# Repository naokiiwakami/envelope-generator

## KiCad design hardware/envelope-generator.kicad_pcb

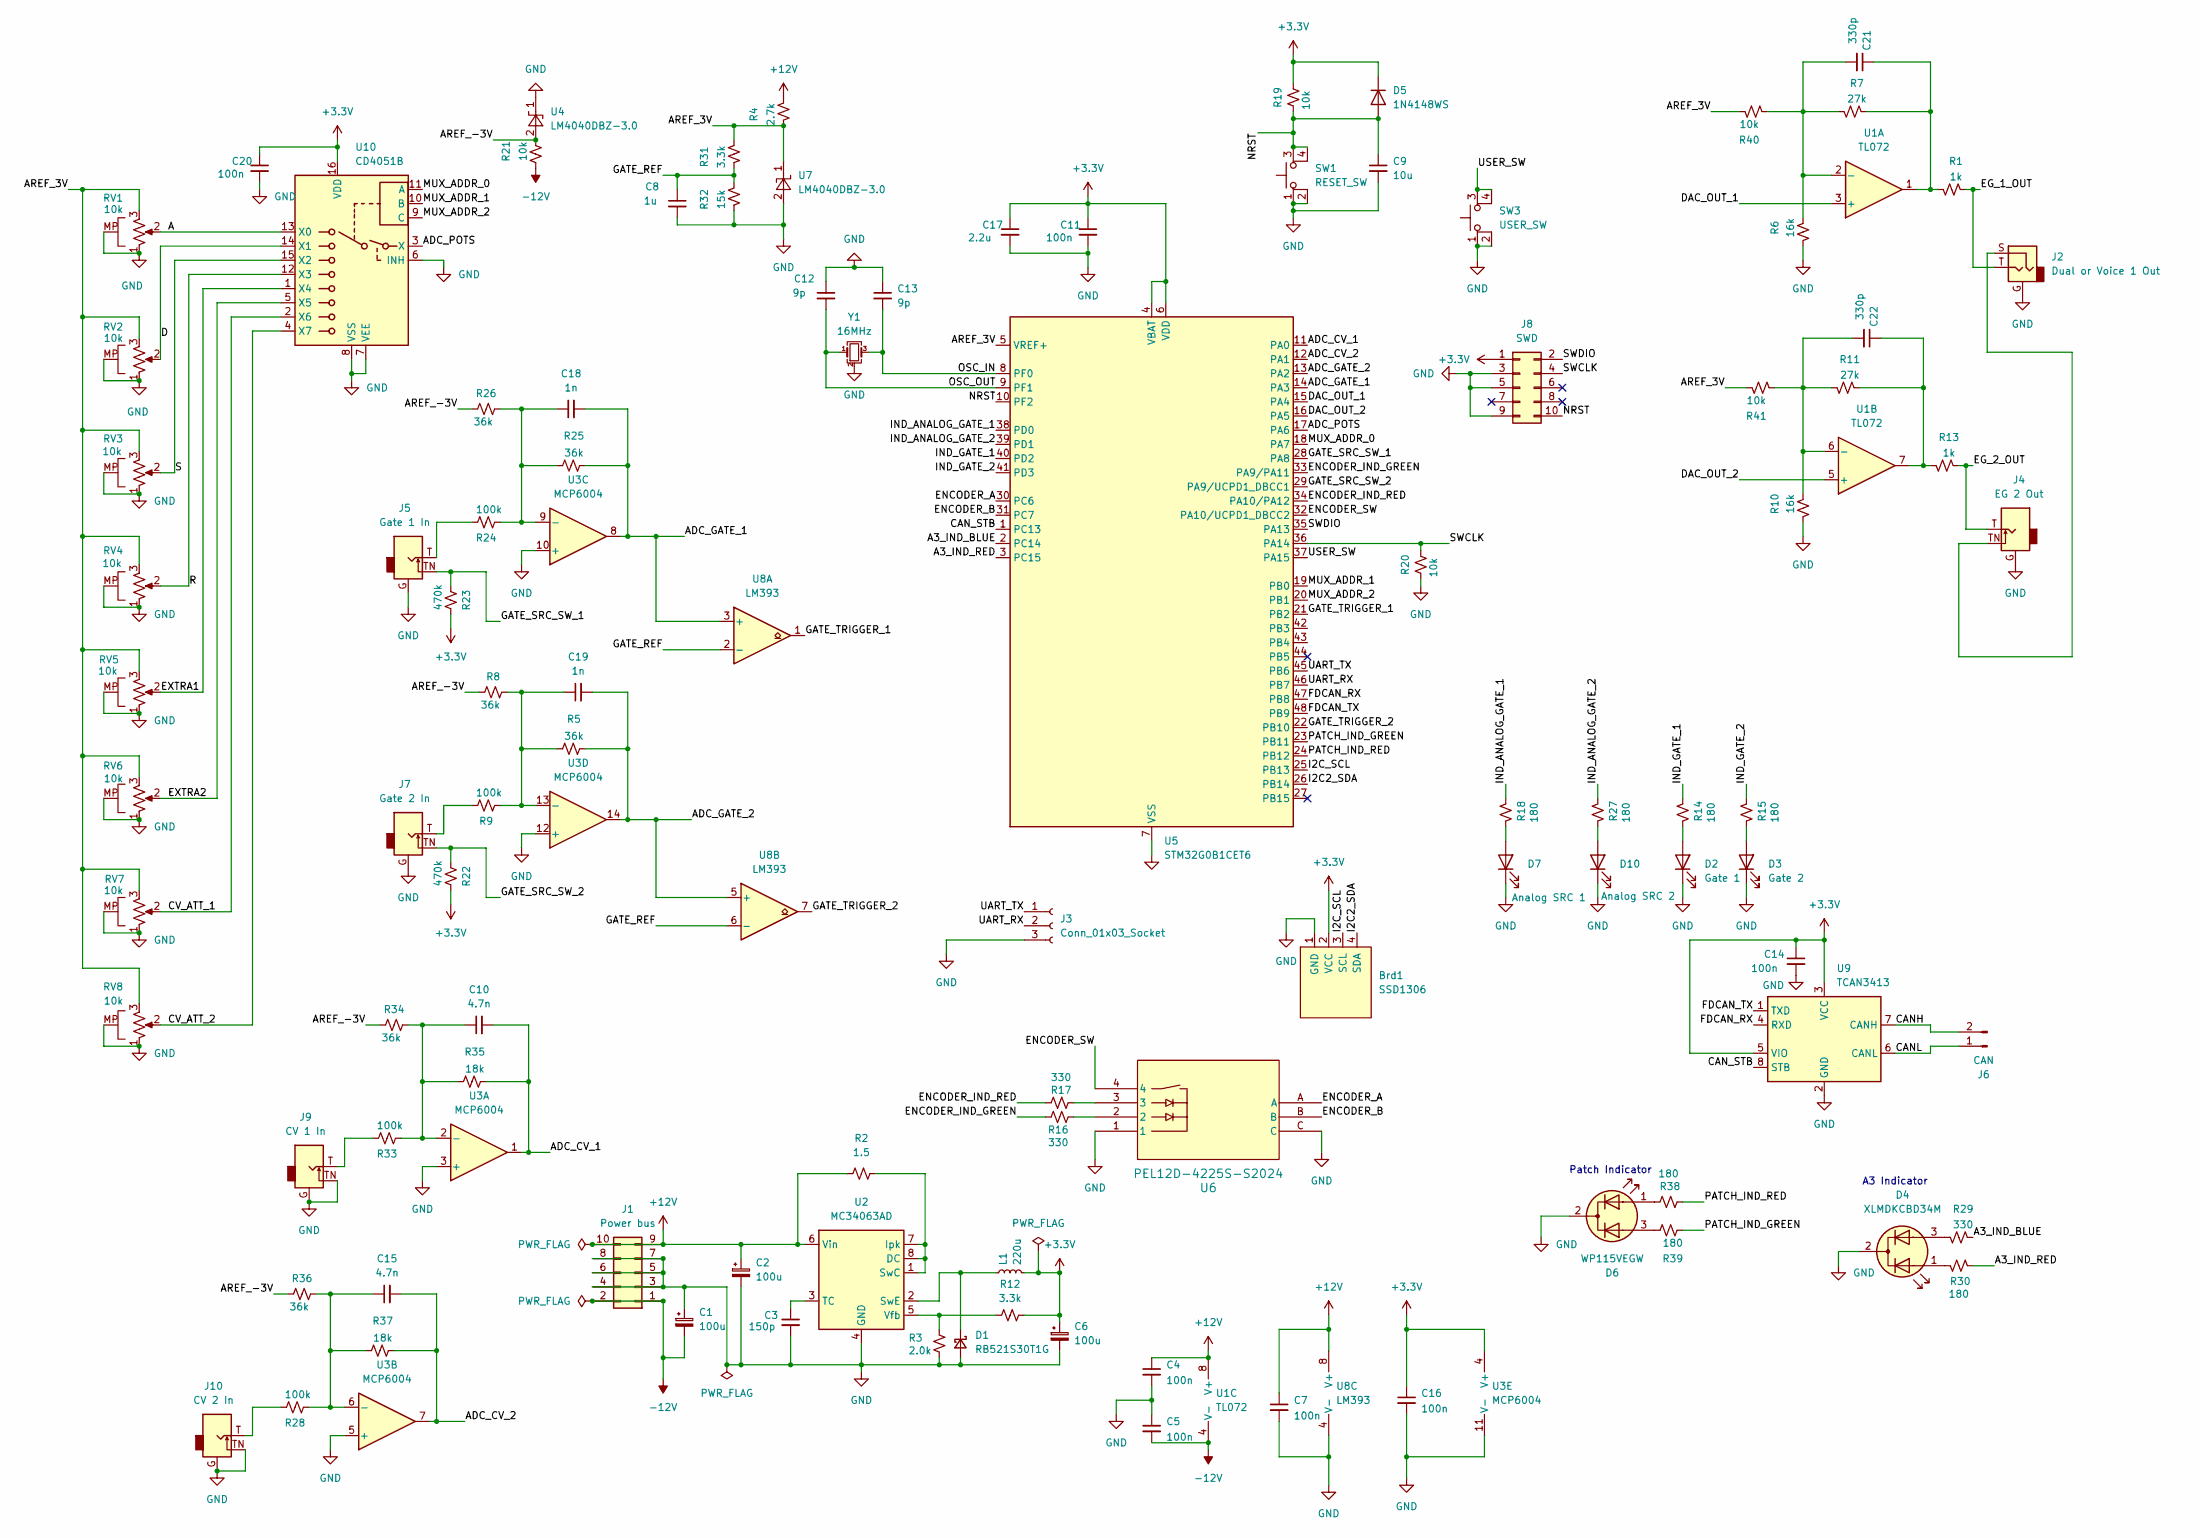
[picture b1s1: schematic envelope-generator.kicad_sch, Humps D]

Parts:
Brd1: SSD1306; 128x64OLED_aki
C1, C2, C6: 100u; CP_Elec_6.3x5.4_Nichicon
C3: 150p; C_0603_1608Metric
C4, C5, C7, C16: 100n; C_0603_1608Metric
C8: 1u; C_0603_1608Metric_Pad1.08x0.95mm_HandSolder
C9: 10u; C_0805_2012Metric
C10, C15: 4.7n; C_0603_1608Metric_Pad1.08x0.95mm_HandSolder
C11, C14, C20: 100n; C_0603_1608Metric_Pad1.08x0.95mm_HandSolder
C12, C13: 9p; C_0603_1608Metric_Pad1.08x0.95mm_HandSolder
C17: 2.2u; C_0603_1608Metric_Pad1.08x0.95mm_HandSolder
C18, C19: 1n; C_0603_1608Metric_Pad1.08x0.95mm_HandSolder
C21, C22: 330p; C_0603_1608Metric_Pad1.08x0.95mm_HandSolder
D1: RB521S30T1G; D_SOD-523
D2: Gate 1; LED_D3.0mm
D3: Gate 2; LED_D3.0mm
D4: XLMDKCBD34M; LED-3.0mm-3
D5: 1N4148WS; D_SOD-323
D6: WP115VEGW; LED-3.0mm-3
D7: Analog SRC 1; LED_D3.0mm
D10: Analog SRC 2; LED_D3.0mm
J1: Power bus; IDC-Header_2x05_P2.54mm_Vertical
J2: Dual or Voice 1 Out; Thonkiconn_Stereo
J3: Conn_01x03_Socket; PinSocket_1x03_P1.27mm_Vertical
J4: EG 2 Out; Thonkiconn
J5: Gate 1 In; Thonkiconn
J6: CAN; Molex_KK-254_AE-6410-02A_1x02_P2.54mm_Vertical
J7: Gate 2 In; Thonkiconn
J8: SWD; CONN_2x10_3220-10-0100-00_CNC
J9: CV 1 In; Thonkiconn
J10: CV 2 In; Thonkiconn
L1: 220u; L_1210_3225Metric
R1, R13: 1k; R_0603_1608Metric
R2: 1.5; R_0603_1608Metric
R3: 2.0k; R_0603_1608Metric
R4: 2.7k; R_0603_1608Metric_Pad0.98x0.95mm_HandSolder
R5, R8, R25, R26, R34, R36: 36k; R_0603_1608Metric_Pad0.98x0.95mm_HandSolder
R6, R10: 16k; R_0603_1608Metric
R7, R11: 27k; R_0603_1608Metric
R9, R24, R28, R33: 100k; R_0603_1608Metric_Pad0.98x0.95mm_HandSolder
R12: 3.3k; R_0603_1608Metric
R14, R15, R18, R27, R30: 180; R_0603_1608Metric
R16, R17, R29: 330; R_0603_1608Metric
R19, R20, R21: 10k; R_0603_1608Metric_Pad0.98x0.95mm_HandSolder
R22, R23: 470k; R_0603_1608Metric_Pad0.98x0.95mm_HandSolder
R31: 3.3k; R_0603_1608Metric_Pad0.98x0.95mm_HandSolder
R32: 15k; R_0603_1608Metric_Pad0.98x0.95mm_HandSolder
R35, R37: 18k; R_0603_1608Metric_Pad0.98x0.95mm_HandSolder
R38, R39: 180; R_0603_1608Metric_Pad0.98x0.95mm_HandSolder
R40, R41: 10k; R_0603_1608Metric
RV1, RV2, RV3, RV4, RV5, RV6, RV7, RV8: 10k; ALPHA_9MM
SW1: RESET_SW; Panasonic_EVQ_Q2
SW3: USER_SW; SW4_1825910-B_TEC
U1: TL072; SOT-23-8
U2: MC34063AD; SOIC-8_3.9x4.9mm_P1.27mm
U3: MCP6004; SOIC-14_3.9x8.7mm_P1.27mm
U4, U7: LM4040DBZ-3.0; SOT-23
U5: STM32G0B1CET6; LQFP-48_7x7mm_P0.5mm
U6: PEL12D-4225S-S2024; TO_4225S-S2024
U8: LM393; SOIC-8_3.9x4.9mm_P1.27mm
U9: TCAN3413; TSOT-23-8
U10: CD4051B; TSSOP-16_4.4x5mm_P0.65mm
Y1: 16MHz; Crystal_SMD_Abracon_ABM8G-4Pin_3.2x2.5mm

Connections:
+3.3V: Brd1.2 (VCC), C6.1, C11.1, C14.1, C16.1, C17.1, C20.1, D5.1 (K), J8.1, L1.2, R12.1, R19.2, R22.2, R23.2, U3.4 (V+), U5.4 (VBAT), U5.6 (VDD), U9.3 (VCC), U9.5 (VIO), U10.16 (VDD)
+12V: C2.1, C4.1, C7.1, J1.9, J1.10, R2.1, R4.2, U1.8 (V+), U2.6 (Vin), U8.8 (V+)
-12V: C1.2, C5.2, J1.1, J1.2, R21.2, U1.4 (V-)
/A: RV1.2, U10.13 (X0)
/A3_IND_BLUE: R29.1, U5.2 (PC14)
/A3_IND_RED: R30.1, U5.3 (PC15)
/ADC_CV_1: C10.2, R35.1, U3.1, U5.11 (PA0)
/ADC_CV_2: C15.2, R37.1, U3.7, U5.12 (PA1)
/ADC_GATE_1: C18.2, R25.1, U3.8, U5.14 (PA3), U8.3 (+)
/ADC_GATE_2: C19.2, R5.1, U3.14, U5.13 (PA2), U8.5 (+)
/ADC_POTS: U5.17 (PA6), U10.3 (X)
/AREF_3V: R4.1, R31.2, R40.1, R41.1, RV1.3, RV2.3, RV3.3, RV4.3, RV5.3, RV6.3, RV7.3, RV8.3, U5.5 (VREF+), U7.1 (K)
/AREF_-3V: R8.1, R21.1, R26.1, R34.1, R36.1, U4.2 (A)
/CANH: J6.2, U9.7 (CANH)
/CANL: J6.1, U9.6 (CANL)
/CAN_STB: U5.1 (PC13), U9.8 (STB)
/CV_ATT_1: RV7.2, U10.2 (X6)
/CV_ATT_2: RV8.2, U10.4 (X7)
/D: RV2.2, U10.14 (X1)
/DAC_OUT_1: U1.3 (+), U5.15 (PA4)
/DAC_OUT_2: U1.5 (+), U5.16 (PA5)
/EG_1_OUT: J2.T, R1.1
/EG_2_OUT: J4.T, R13.1
/ENCODER_A: U5.30 (PC6), U6.A
/ENCODER_B: U5.31 (PC7), U6.B
/ENCODER_IND_GREEN: R16.1, U5.33 (PA9/PA11)
/ENCODER_IND_RED: R17.2, U5.34 (PA10/PA12)
/ENCODER_SW: U5.32 (PA10/UCPD1_DBCC2), U6.4
/EXTRA1: RV5.2, U10.1 (X4)
/EXTRA2: RV6.2, U10.5 (X5)
/FDCAN_RX: U5.47 (PB8), U9.4 (RXD)
/FDCAN_TX: U5.48 (PB9), U9.1 (TXD)
/GATE_REF: C8.1, R31.1, R32.2, U8.2 (-), U8.6 (-)
/GATE_SRC_SW_1: J5.TN, R23.1, U5.28 (PA8)
/GATE_SRC_SW_2: J7.TN, R22.1, U5.29 (PA9/UCPD1_DBCC1)
/GATE_TRIGGER_1: U5.21 (PB2), U8.1
/GATE_TRIGGER_2: U5.22 (PB10), U8.7
/I2C2_SDA: Brd1.4 (SDA), U5.26 (PB14)
/I2C_SCL: Brd1.3 (SCL), U5.25 (PB13)
/IND_ANALOG_GATE_1: R18.1, U5.38 (PD0)
/IND_ANALOG_GATE_2: R27.1, U5.39 (PD1)
/IND_GATE_1: R14.1, U5.40 (PD2)
/IND_GATE_2: R15.1, U5.41 (PD3)
/MUX_ADDR_0: U5.18 (PA7), U10.11 (A)
/MUX_ADDR_1: U5.19 (PB0), U10.10 (B)
/MUX_ADDR_2: U5.20 (PB1), U10.9 (C)
/NRST: C9.1, D5.2 (A), J8.10, R19.1, SW1.3, SW1.4, U5.10 (PF2)
/OSC_IN: C13.2, U5.8 (PF0), Y1.3
/OSC_OUT: C12.2, U5.9 (PF1), Y1.1
/PATCH_IND_GREEN: R39.1, U5.23 (PB11)
/PATCH_IND_RED: R38.1, U5.24 (PB12)
/R: RV4.2, U10.12 (X3)
/S: RV3.2, U10.15 (X2)
/SWCLK: J8.4, R20.2, U5.36 (PA14)
/SWDIO: J8.2, U5.35 (PA13)
/UART_RX: J3.2, U5.46 (PB7)
/UART_TX: J3.1, U5.45 (PB6)
/USER_SW: SW3.3, SW3.4, U5.37 (PA15)
GND: Brd1.1 (GND), C1.1, C2.2, C3.2, C4.2, C5.1, C6.2, C7.2, C8.2, C9.2, C11.2, C12.1, C13.1, C14.2, C16.2, C17.2, C20.2, D1.2 (A), D2.1 (K), D3.1 (K), D4.2 (K), D6.2 (K), D7.1 (K), D10.1 (K), J1.3, J1.4, J1.5, J1.6, J1.7, J1.8, J2.G, J3.3, J4.G, J5.G, J7.G, J8.3, J8.5, J8.9, J9.G, J9.TN, J10.G, J10.TN, R3.1, R6.2, R10.2, R20.1, R32.1, RV1.1, RV1.MP, RV2.1, RV2.MP, RV3.1, RV3.MP, RV4.1, RV4.MP, RV5.1, RV5.MP, RV6.1, RV6.MP, RV7.1, RV7.MP, RV8.1, RV8.MP, SW1.1, SW1.2, SW3.1, SW3.2, U2.4 (GND), U3.3 (+), U3.5 (+), U3.10 (+), U3.11 (V-), U3.12 (+), U4.1 (K), U5.7 (VSS), U6.1, U6.C, U7.2 (A), U8.4 (V-), U9.2 (GND), U10.6 (INH), U10.7 (VEE), U10.8 (VSS), Y1.2 (G), Y1.4 (G)
unnamed: C21.1, R1.2, R7.1, U1.1
unnamed: C22.1, R11.1, R13.2, U1.7
unnamed: D1.1 (K), L1.1, U2.2 (SwE)
unnamed: D2.2 (A), R14.2
unnamed: D3.2 (A), R15.2
unnamed: D4.1 (A1), R30.2
unnamed: D4.3 (A2), R29.2
unnamed: D6.1 (A1), R38.2
unnamed: D6.3 (A2), R39.2
unnamed: D7.2 (A), R18.2
unnamed: D10.2 (A), R27.2
unnamed: J2.S, J4.TN
unnamed: J5.T, R24.2
unnamed: J7.T, R9.2
unnamed: J9.T, R33.2
unnamed: J10.T, R28.2
unnamed: R16.2, U6.2
unnamed: R17.1, U6.3
unnamed: C21.2, R6.1, R7.2, R40.2, U1.2 (-)
unnamed: C22.2, R10.1, R11.2, R41.2, U1.6 (-)
unnamed: R2.2, U2.1 (SwC), U2.7 (Ipk), U2.8 (DC)
unnamed: C3.1, U2.3 (TC)
unnamed: R3.2, R12.2, U2.5 (Vfb)
unnamed: C10.1, R33.1, R34.2, R35.2, U3.2 (-)
unnamed: C15.1, R28.1, R36.2, R37.2, U3.6 (-)
unnamed: C18.1, R24.1, R25.2, R26.2, U3.9 (-)
unnamed: C19.1, R5.2, R8.2, R9.1, U3.13 (-)

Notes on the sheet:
Patch Indicator
A3 Indicator

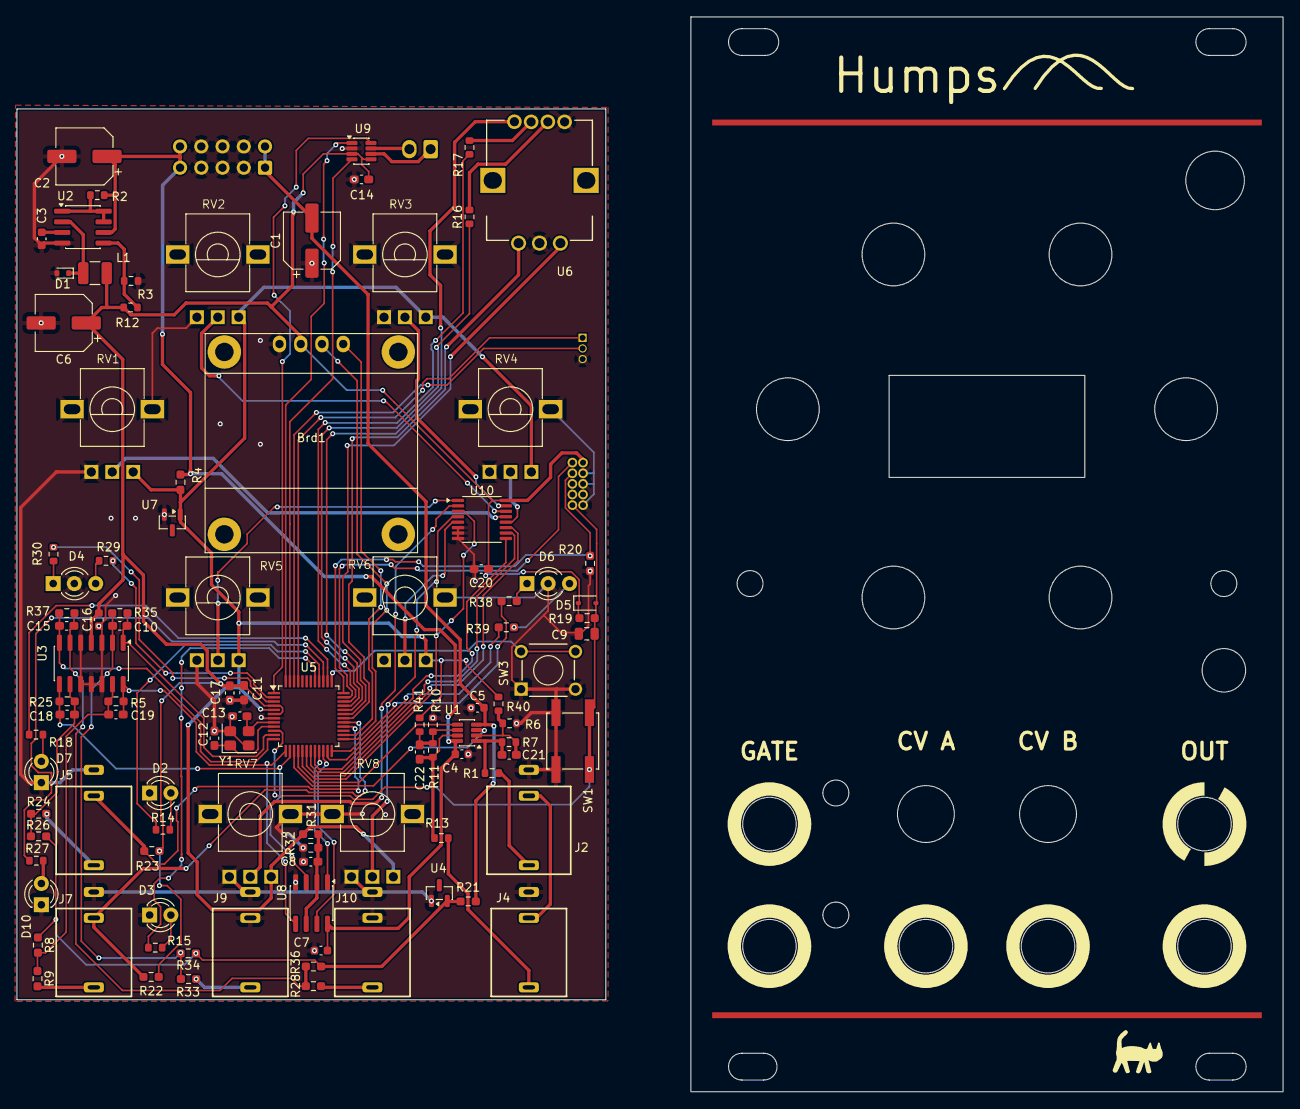
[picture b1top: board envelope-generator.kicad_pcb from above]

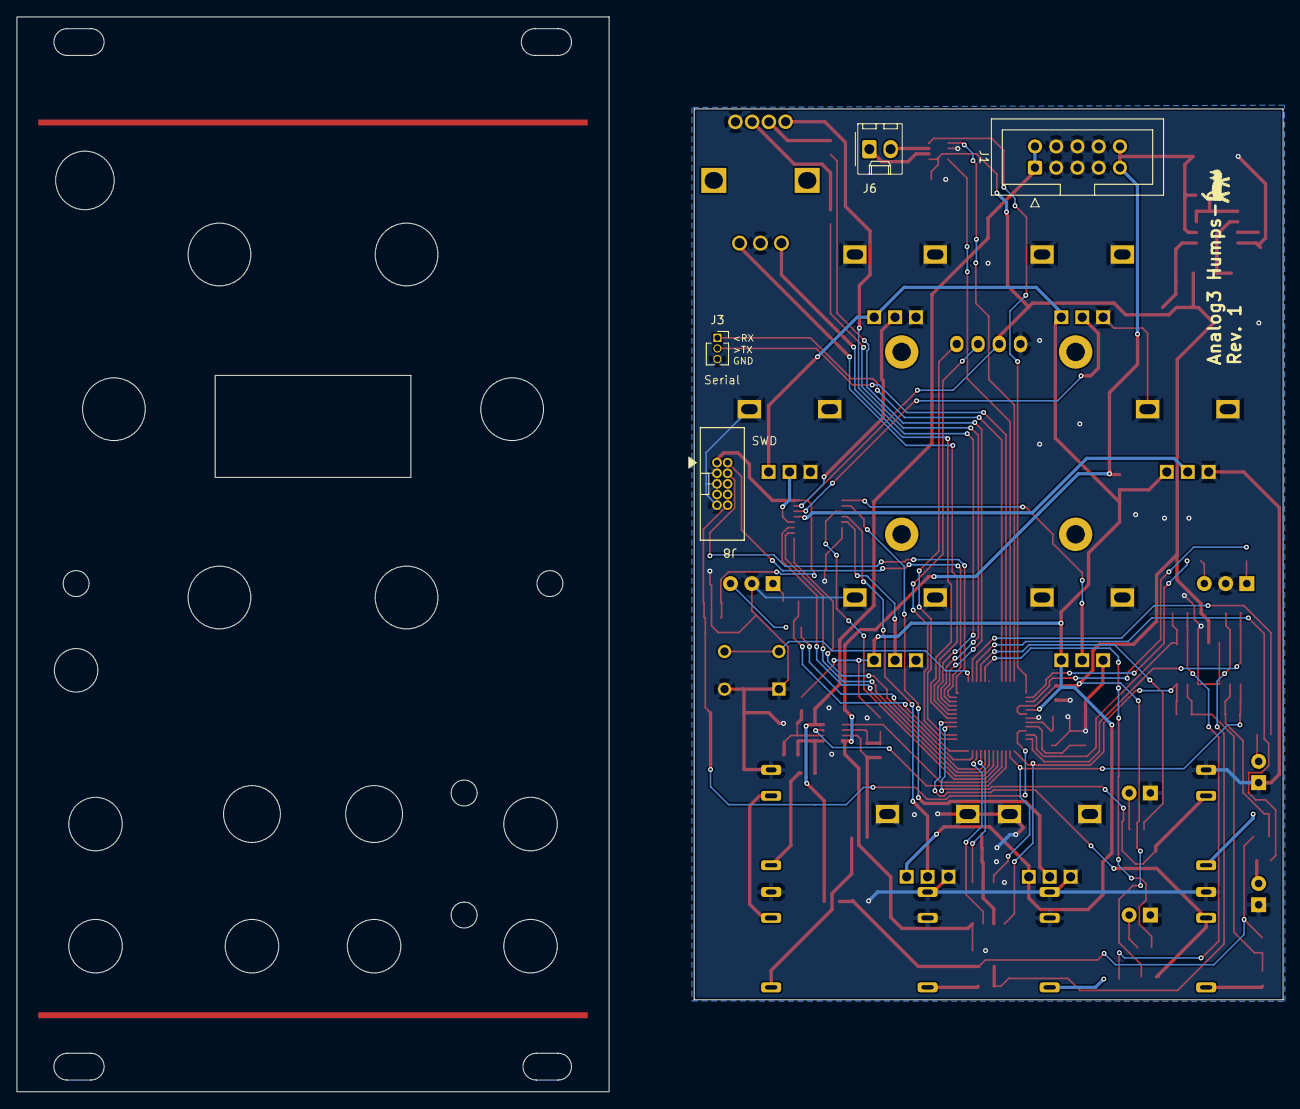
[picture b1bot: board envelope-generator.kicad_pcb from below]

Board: 2 copper layers, 70.4 x 106.5 mm, 105 parts (4 on the bottom side), 86 nets.

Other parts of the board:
SSD1306: 128x64OLED; 128x64 OLED Window

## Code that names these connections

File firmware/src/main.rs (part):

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
async fn setup_peripherals(p: Peripherals) -> EgResources {
    // can standby controller pin
    let mut can_stb = Output::new(p.PC13, Level::High, Speed::Low);

    // disable the CAN transceiver
    can_stb.set_high();

    // A3 indicators
    let ind_a3_red = Output::new(p.PC15, Level::Low, Speed::Low);
    let ind_a3_blue = Output::new(p.PC14, Level::Low, Speed::Low);

    // gate status indicator
    let ind_gate_1 = Output::new(p.PD2, Level::Low, Speed::Low);
    let ind_gate_2 = Output::new(p.PD3, Level::Low, Speed::Low);

    // input source
    let ind_analog_gate_1 = Output::new(p.PD0, Level::Low, Speed::Low);
    let ind_analog_gate_2 = Output::new(p.PD1, Level::Low, Speed::Low);
    let gate_src_sw_1 = Input::new(p.PA8, Pull::None);
    let gate_src_sw_2 = Input::new(p.PA9, Pull::None);

    // physical gate trigger
    let gate_trigger_1 = ExtiInput::new(p.PB2, p.EXTI2, Pull::Up, ExtiIrqsGate1);
    let gate_trigger_2 = ExtiInput::new(p.PB10, p.EXTI10, Pull::Up, ExtiIrqsGate2);

    // user switch
    let patch_button = Input::new(p.PA15, Pull::Up);

    // patch indicator
    let patch_ind_red = Output::new(p.PB12, Level::Low, Speed::Low);
    let patch_ind_green = Output::new(p.PB11, Level::Low, Speed::Low);

    let flash = Flash::new(p.FLASH, FlashIrqs);

    // start the CAN controller
    let can = {
        let mut can_config = can::CanConfigurator::new(p.FDCAN1, p.PB8, p.PB9, CanIrqs);
        let nominal_bitrate = 1_000_000;
        let data_bitrate = 4_000_000;
        debug!(
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        i2c_config.frequency = Hertz(1_000_000);

        let i2c_peri = p.I2C2;
        let scl = p.PB13;
        let sda = p.PB14;
        let tx_dma = p.DMA1_CH4;
        let rx_dma = p.DMA1_CH5;
        I2c::new(i2c_peri, scl, sda, tx_dma, rx_dma, I2cIrqs, i2c_config)
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    unsafe { cortex_m::peripheral::NVIC::unmask(interrupt::TIM2) };

    // DAC
    let dac_channels = Dac::new_blocking(p.DAC1, p.PA4, p.PA5);
    // enable triggers
    pac::DAC1.cr().modify(|w| {
        w.set_ten(0, true);
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
    // ADC
    let adc = Adc::new(p.ADC1);
    let mux_addr_0 = Output::new(p.PA7, Level::Low, Speed::Medium);
    let mux_addr_1 = Output::new(p.PB0, Level::Low, Speed::Medium);
    let mux_addr_2 = Output::new(p.PB1, Level::Low, Speed::Medium);
    let dma = p.DMA1_CH1;
    let adc_resources = input_reader::AdcResources {
        adc,
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        mux_addr_1,
        mux_addr_2,

        pots: p.PA6,

        gate_1: p.PA3,
        gate_2: p.PA2,

        cv_a: p.PA0,
        cv_b: p.PA1,
    };

    let mut qei_config = qei::Config::default();
    qei_config.ch1_pull = Pull::Up;
    qei_config.ch2_pull = Pull::Up;
    let encoder = Qei::new(p.TIM3, p.PC6, p.PC7, qei_config);
    let encoder_button = Input::new(p.PA10, Pull::Up);
    let encoder_ind_red = Output::new(p.PA12, Level::Low, Speed::Low);
    let encoder_ind_green = Output::new(p.PA11, Level::Low, Speed::Low);

    EgResources {
        can,
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
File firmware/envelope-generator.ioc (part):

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Mcu.Name=STM32C092KCTx
Mcu.Package=LQFP32
Mcu.UserName=STM32C092KCTx
PA0.GPIOParameters=GPIO_Label
PA0.GPIO_Label=ADC_A
PA0.Mode=IN0
PA0.Signal=ADC1_IN0
PA1.GPIOParameters=GPIO_Label
PA1.GPIO_Label=ADC_D
PA1.Mode=IN1
PA1.Signal=ADC1_IN1
PA10.GPIOParameters=GPIO_Label
PA10.GPIO_Label=IND_ANALOG_GATE
PA10.Signal=GPIO_Output
PA11\ [PA9].GPIOParameters=GPIO_Label
PA11\ [PA9].GPIO_Label=IND_EG_MODE_1
PA11\ [PA9].Signal=GPIO_Output
PA12\ [PA10].GPIOParameters=GPIO_Label
PA12\ [PA10].GPIO_Label=IND_EG_MODE_0
PA12\ [PA10].Signal=GPIO_Output
PA13.Mode=Serial_Wire
PA13.Signal=DEBUG_SWDIO
PA14-BOOT0.Mode=Serial_Wire
PA14-BOOT0.Signal=DEBUG_SWCLK
PA15.GPIOParameters=GPIO_Label
PA15.GPIO_Label=IND_GATE_2
PA15.Signal=GPIO_Output
PA2.GPIOParameters=GPIO_Label
PA2.GPIO_Label=ADC_S
PA2.Mode=IN2
PA2.Signal=ADC1_IN2
PA3.GPIOParameters=GPIO_Label
PA3.GPIO_Label=ADC_R
PA3.Mode=IN3
PA3.Signal=ADC1_IN3
PA4.GPIOParameters=GPIO_Label
PA4.GPIO_Label=ADC_D0
PA4.Mode=IN4
PA4.Signal=ADC1_IN4
PA5.GPIOParameters=GPIO_Label
PA5.GPIO_Label=ADC_S0
PA5.Mode=IN5
PA5.Signal=ADC1_IN5
PA6.GPIOParameters=GPIO_Label
PA6.GPIO_Label=ADC_GATE_1
PA6.Mode=IN6
PA6.Signal=ADC1_IN6
PA7.GPIOParameters=GPIO_Label
PA7.GPIO_Label=ADC_GATE_2
PA7.Mode=IN7
PA7.Signal=ADC1_IN7
PA8.Mode=Asynchronous
PA8.Signal=USART1_RX
PA9.Mode=Asynchronous
PA9.Signal=USART1_TX
PB0.GPIOParameters=GPIO_PuPd,GPIO_Label
PB0.GPIO_Label=SW_EG_MODE
PB0.GPIO_PuPd=GPIO_PULLUP
PB0.Signal=GPIO_Input
PB1.GPIOParameters=GPIO_Label
PB1.GPIO_Label=A3_IND_RED
PB1.Signal=GPIO_Output
PB2.GPIOParameters=GPIO_Label
PB2.GPIO_Label=A3_IND_BLUE
PB2.Signal=GPIO_Output
PB3.GPIOParameters=GPIO_Label
PB3.GPIO_Label=IND_GATE_1
PB3.Signal=GPIO_Output
PB4.GPIOParameters=GPIO_Label
PB4.GPIO_Label=CAN_STB
PB4.Signal=GPIO_Input
PB5.Mode=FDCAN_Activate
PB5.Signal=FDCAN1_RX
PB6.GPIOParameters=GPIO_Speed,GPIO_FM6
PB6.GPIO_FM6=__NULL
PB6.GPIO_Speed=GPIO_SPEED_FREQ_VERY_HIGH
PB6.Mode=FDCAN_Activate
PB6.Signal=FDCAN1_TX
PB7.Signal=S_TIM3_CH4
PB8.Signal=S_TIM3_CH1
PB9.GPIOParameters=GPIO_Label
PB9.GPIO_Label=SW_GATE_2
PB9.Signal=GPIO_Input
PC14-OSCX_IN(PC14).Mode=HSE-External-Oscillator
PC14-OSCX_IN(PC14).Signal=RCC_OSCX_IN
PC15-OSCX_OUT(PC15).Mode=HSE-External-Oscillator
PC15-OSCX_OUT(PC15).Signal=RCC_OSCX_OUT
PC6.GPIOParameters=GPIO_PuPd,GPIO_Label
PC6.GPIO_Label=SW_GATE_SRC
PC6.GPIO_PuPd=GPIO_PULLUP
PC6.Signal=GPIO_Input
RCC.HSE_VALUE=48000000
RCC.SYSCLKFreq_VALUE=48000000
board=custom

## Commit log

2025-11-03 Introduce new component 'EnvelopeGenerator'
2025-11-03 Generalize MCP47x6 DAC handling methods
2025-11-05 Make release time configurable
2025-11-06 Initial ADSR implementation
2025-11-06 minor fixes
2025-11-07 Improve mechanism to update envelope generator units to eliminate intermittent pop noises
2025-11-07 Fix bugs
2025-11-07 Double precision of envelope calculation
2025-11-07 bugfix
2025-11-10 Avoid calculations in interrupt handlers
2025-11-10 try ADDSR
2025-11-10 Try PWM
2025-11-11 Consolidate timer to update EG to TIM3 to avoid potential risk of beating effect
2025-11-11 Try decay distortion
2025-11-12 Add support for analog gate input
2025-11-18 Save before eliminating I2C for ADC
2025-11-20 Eliminate I2C for DAC
2025-11-26 Build prototyping board
2025-11-26 Add an offset of 1/32 level to avoid silence with low velocity
2025-11-26 fix bug in submitting a task
2025-11-27 implement decay distortion
2025-11-28 Add the second EG unit
2025-11-28 Eliminate rounding ADC values
2025-11-28 Split eg1 and eg2 parameter sets
2025-11-28 Add mode change switch
2025-11-29 add two phase decay mode
2025-11-29 Add linear mode
2025-11-29 Extend maximum number of EG modes to 8
2025-11-30 add gritty mode
2025-11-30 Merge PoC code (#1)
    * initial commit
    * Introduce new component 'EnvelopeGenerator'
    * Generalize MCP47x6 DAC handling methods
    * Make release time configurable
    * Initial ADSR implementation
    * minor fixes
2025-12-01 set up properties, wip
2025-12-02 set up properties, initial implementation
2025-12-02 add support for renaming
2025-12-03 Fix bugs in remote configuration
2026-02-09 code cleansing
2026-02-15 PCB design the first iteration
2026-03-13 humps rev 0
2026-03-13 Move firmware to firmware-poc for reference
2026-03-13 humps firmware initial commit
2026-03-13 Fix build issue
2026-03-13 Refactor before proceeding for the next step
2026-03-13 modularize diagnoser
2026-03-13 Split display menu mode out
2026-03-13 Make menu display mode a generic
2026-03-13 Remove unused imports
2026-03-13 (try to) fix bug in menu index tracking
2026-03-14 Add operation menu
2026-03-14 Implemented ADDSR
2026-03-16 Add functionality to switch EG type
2026-03-16 Reorganize files
2026-03-16 Add linear EG engine
2026-03-16 Add diag EG engine
2026-03-17 Enlarge menu font
2026-03-17 enable get-config
2026-03-17 Remove rough edges around CV reading
2026-03-17 Enable Diag engine
2026-03-17 Eliminate the term event around EG request
2026-03-18 Enable showing current engine type
2026-03-18 Ensure module instances are created on the main task
2026-03-18 Add basic framework to display for each engine type
2026-03-18 Start using fixed
2026-03-18 Replace values in ADSR engine by fixed types
2026-03-18 Use fixed for the ADDSR engine
2026-03-18 Reverse the polarity of delta
2026-03-18 Rename AddsrEngine to TwoDecaysEngine
2026-03-18 Issue 6 (#10)
    * Add basic framework to display for each engine type
    * Start using fixed
    * Replace values in ADSR engine by fixed types
    * Use fixed for the ADDSR engine
    * Reverse the polarity of delta
    * Rename AddsrEngine to TwoDecaysEngine
2026-03-18 Simplify TwoDecay engine further
2026-03-19 fix a bug in displaying pot position
2026-03-19 Issue #11 - Simplify the ADSR engine implementation
2026-03-19 Issue #2 - Replace watches for receiving reply by signals
2026-03-19 Adding adsr-dd, wip
2026-03-20 issue #16 Eliminate dependency on crate fixed
2026-03-20 Done with initial implementation of adsr-strum
2026-03-20 done
2026-03-20 Issue #8 Add new engine "ParaDecays" (#17)
    * Adding adsr-dd, wip
    * Done with initial implementation of adsr-strum
    * done
2026-03-24 Replace the display driver by the developed Ssd1306Lite
2026-03-24 Update dependency
2026-03-24 Issue #9 - Replace the display driver by developed Ssd1306Lite (#19)
    * Replace the display driver by the developed Ssd1306Lite
    * Update dependency
2026-03-24 upgrade embassy
2026-03-25 Fixed dependency issues
2026-03-25 Issue #18 - Upgrade Embassy (#20)
    * upgrade embassy
    * Fixed dependency issues
2026-03-25 Modify the circuit to enable negative output
2026-03-25 Modify engines to support positive and negative output
2026-03-25 Improve the way to write value to DAC
2026-03-25 Issue #4 - Add capability for negative output (#22)
    * Modify the circuit to enable negative output
    * Modify engines to support positive and negative output
    * Improve the way to write value to DAC
2026-03-25 Add calibrator, wip
2026-03-26 Add capability to calibrate the module, wip
2026-03-26 Calibration, wip #2
2026-03-26 Improve appearance
2026-03-27 remove a done TODO comment
2026-03-27 Issue #13 - Add capability to calibrate the module (#24)
    * Add calibrator, wip
    * Add capability to calibrate the module, wip
    * Calibration, wip #2
    * Improve appearance
    * remove a done TODO comment
2026-03-27 wip, storage is unstable yet
2026-03-28 Move analog3 out to a crate
2026-03-29 Issue #3 - Save and load configuration (#27)
    * wip, storage is unstable yet
    * Move analog3 out to a crate
2026-03-29 Remove C++ PoC firmware
2026-03-30 note scaling, wip
2026-03-30 Done with ADSR note tracking
2026-03-31 covered linear engine
2026-03-31 Add para decay coverage
2026-03-31 Add two decays coverage
2026-03-31 Issue #28 Add note scaling (#29)
    * note scaling, wip
    * Done with ADSR note tracking
    * Code cleansing
    * covered linear engine
    * Add para decay coverage
    * Add two decays coverage
2026-03-31 Make new display mode InOperation
2026-03-31 move InOperation display mode to a new file
2026-03-31 introduce a concept of "page" in the control panel
2026-04-01 Remove OpMenu
2026-04-01 Add output polarity page
2026-04-01 building ADSR home, wip
2026-04-02 building ADSR home, wip 2
2026-04-02 rename analog gate to physical gate
2026-04-02 Revert "rename analog gate to physical gate"
    This reverts commit 9c0c7e640c7240c70e493bea17cb47170256096a.
2026-04-02 refactoring: change EG Diag from an engine type to operation mode
2026-04-02 Add toggling diag mode to the admin menu
2026-04-02 Add note scaling display
2026-04-02 drawing ADSR graphic, wip
2026-04-03 drawing ADSR graphic, wip 2
2026-04-03 done with ADSR home page initial implementation
2026-04-03 Issue #30 - Implement ADSR and Linear home pages (#31)
    * Make new display mode InOperation
    * move InOperation display mode to a new file
    * introduce a concept of "page" in the control panel
    * Remove OpMenu
    * Add output polarity page
    * building ADSR home, wip
2026-04-03 SSD1306lite updated
2026-04-03 bugfix - calibration hangs
2026-04-04 wip2
2026-04-04 Issue #26 create UID by random number generator (#34)
2026-04-04 add startup gimmick, wip
2026-04-05 consolidate the splash screen logic to control-panel/display
2026-04-05 Issue #35 - add splash screen (#36)
    * add startup gimmick, wip
    * consolidate the splash screen logic to control-panel/display
    * code cleansing
    ---------
2026-04-06 Add capability to switch output polarity, wip
2026-04-06 Add capability to switch output polarity, wip 2
2026-04-06 done with initial implementation
2026-04-07 Issue #21 - add capability to reverse output (#39)
    * Add capability to switch output polarity, wip
    * Add capability to switch output polarity, wip 2
    * done with initial implementation
    * bugfix
    ---------
2026-04-07 make control panel state shared
2026-04-07 make control panel state shared (#44)
2026-04-07 prepare for implementing CV moulation
2026-04-07 preparation #2
2026-04-07 attempt to put a fix
2026-04-07 wip 2
2026-04-07 wip 3
2026-04-07 let control panel refer to the EG config instead of its own state, still wip
2026-04-07 wip 5
2026-04-07 migrated all ModuleState parameters to EG config
2026-04-07 add note scaling parameter
2026-04-08 done with ADSR
2026-04-08 covered other engines
2026-04-09 implement CV assignment display
2026-04-09 implementing CV assignment, wip
2026-04-09 Done with fundamental behavior in control panel
2026-04-09 save CV destination config in flash memory
2026-04-09 tweak the appearance
2026-04-10 improve appearance, wip
2026-04-10 improve appearance, wip 2
2026-04-10 Issue #42 - Add capability to assign CV destinations (#46)
2026-04-10 move polarity change steps to a separate file
2026-04-10 move polarity change steps to a separate file (#47)
2026-04-10 initial round
2026-04-10 Issue #45 send pot change notifications via EnvelopeGenerator (#48)
2026-04-10 separated home pages
2026-04-10 detoxed AI poison
2026-04-13 para decay home page, wip
2026-04-13 para decay home page, wip 2
2026-04-13 done with para decay home page, initial version
2026-04-13 add center line
2026-04-13 Issue #32 - para decay home page (#49)
    * separated home pages
    * detoxed AI poison
    * para decay home page, wip
    * para decay home page, wip 2
    * done with para decay home page, initial version
    * add center line
2026-04-13 Add punch to ADSR
2026-04-13 improving appearance, wip
2026-04-13 add zero mark to ParaDecays home page
2026-04-14 Improve appearance (#51)
    * improving appearance, wip
    * improve appearance, wip 2
    * add zero mark to ParaDecays home page
    ---------
2026-04-14 display page
2026-04-14 note scaler, wip
2026-04-14 trial-1
2026-04-14 Revert "trial-1"
    This reverts commit 901950596044c482594fc96c3e80a096d7804c77.
2026-04-14 consolidated operation actions into the ControlPanel loop to prevent EG hang
2026-04-14 done initial implementation
2026-04-14 Detox AI poison #1
2026-04-14 Detox AI poison #2
2026-04-14 eliminate some compiler warnings
2026-04-15 fix awkward movement, wip
2026-04-15 fix awkward movement
2026-04-15 Issue #50 Add capability to configure note scaling for ParaDecays and ADDSR (#52)
    * display page
    * note scaler, wip
    * trial-1
    * Revert "trial-1"
    This reverts commit 901950596044c482594fc96c3e80a096d7804c77.
    * done with initial implementation
2026-04-15 initial implementation
2026-04-15 Rename Two Decays
2026-04-15 Issue #33 - Add Two Phases home page (#53)
    * initial implementation
    * code cleansing
    * Rename Two Decays
2026-04-16 Fix circuit and PCB issues
2026-04-17 fix bug that EG hangs while calibration
2026-04-17 Fix two phases home page appearance
2026-04-18 Introduce calibration mode and CalibEngine
2026-04-21 Issue #23 - add gate trigger point calibration (#57)
2026-05-02 Switch embassy to the official one
